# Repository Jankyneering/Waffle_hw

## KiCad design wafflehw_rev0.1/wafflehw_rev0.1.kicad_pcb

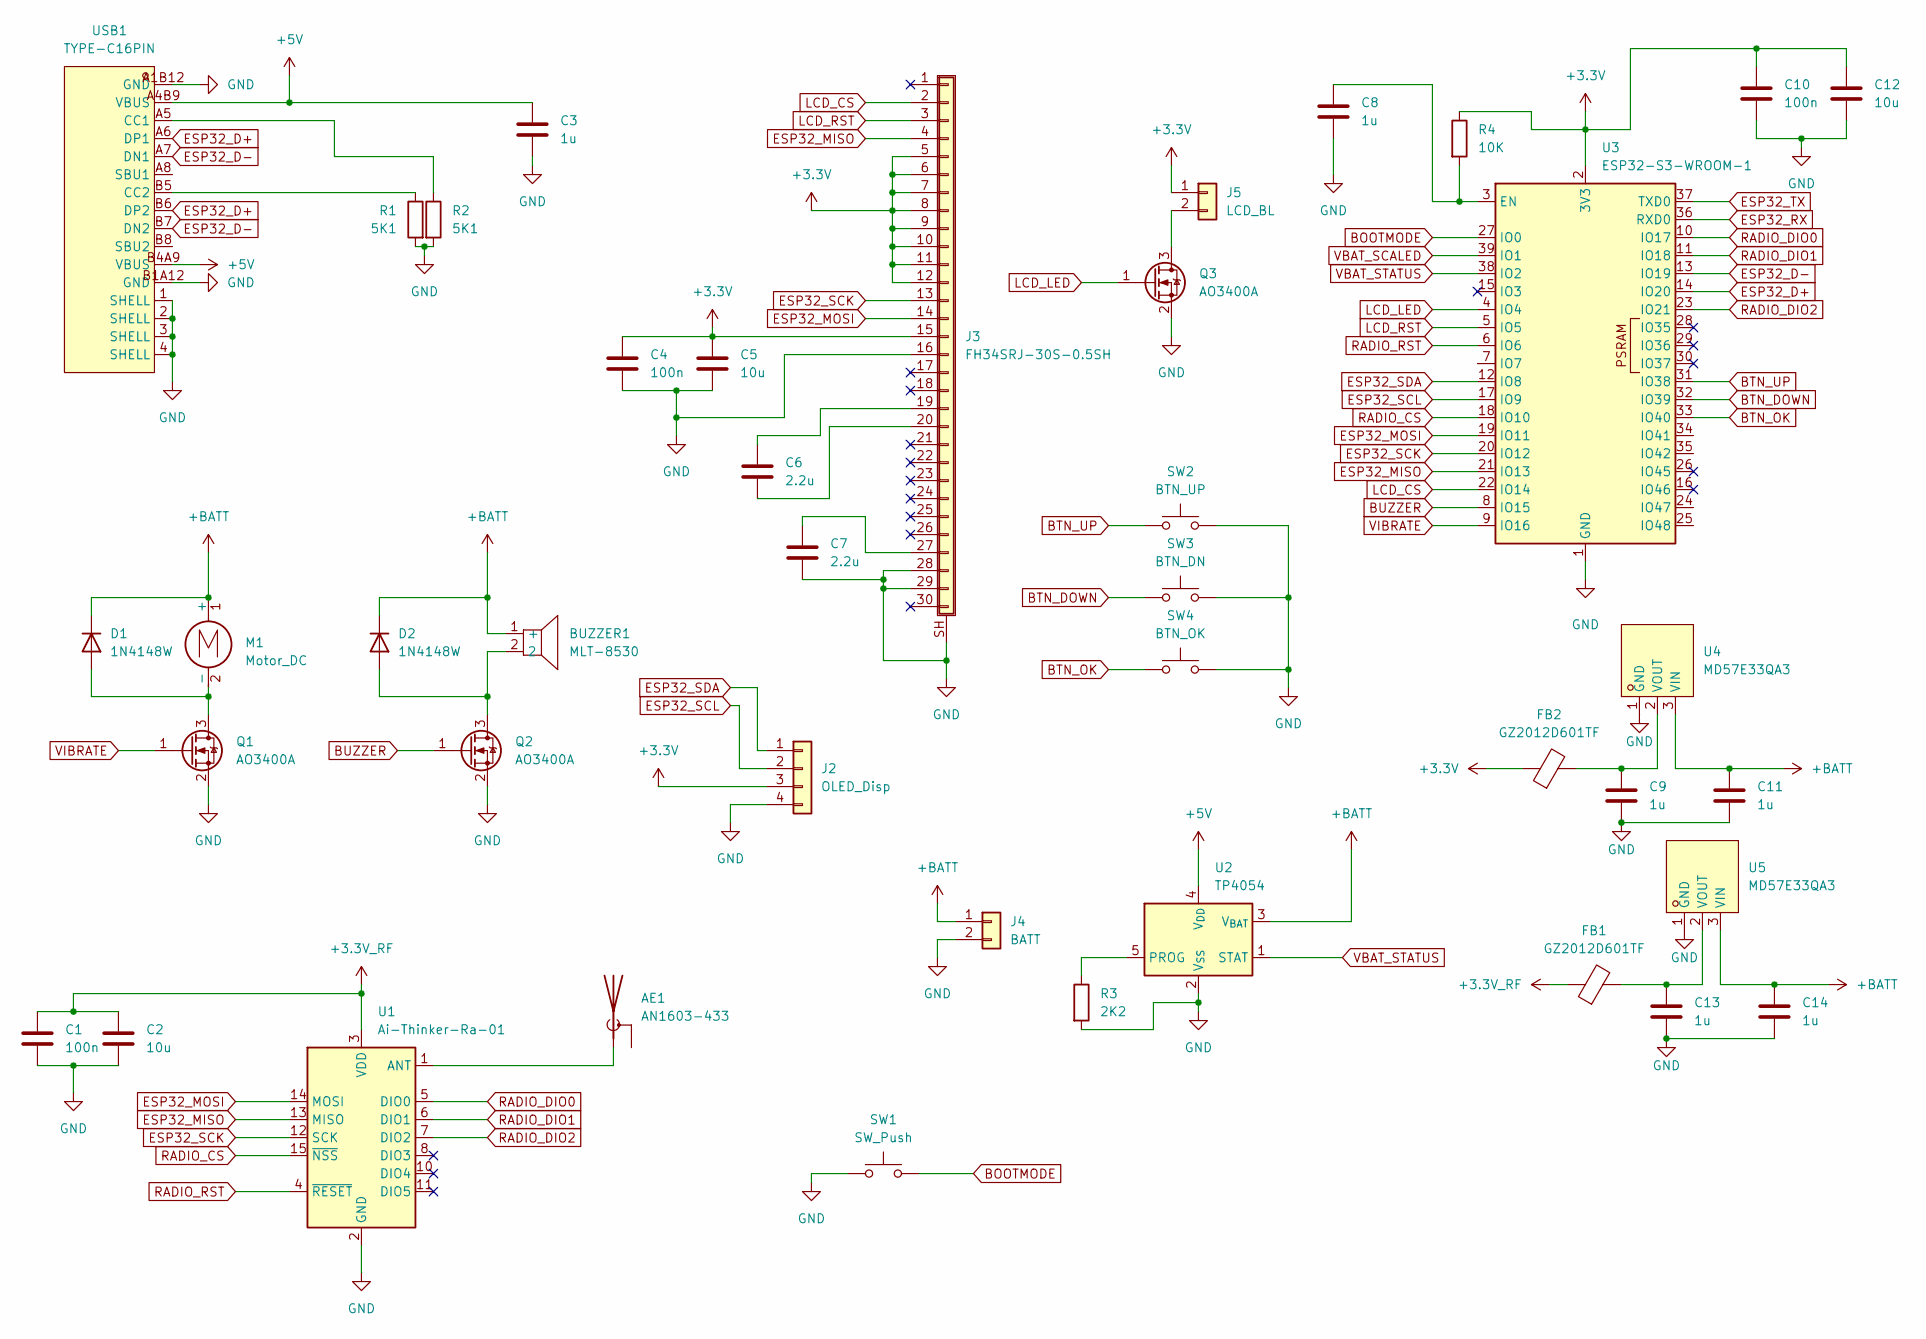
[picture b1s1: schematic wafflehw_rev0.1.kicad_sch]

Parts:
AE1: AN1603-433; Coilcraft_MA5532-AE_RFID
BUZZER1: MLT-8530; BUZ-SMD_4P-L8.5-W8.5-P8.50-BR; LCSC Part C94599
C1, C4, C10: 100n; C_0805_2012Metric
C2, C5, C12: 10u; C_0805_2012Metric
C3, C8, C9, C11, C13, C14: 1u; C_0805_2012Metric
C6, C7: 2.2u; C_0805_2012Metric
D1, D2: 1N4148W; D_SOD-123
FB1, FB2: GZ2012D601TF; L_0805_2012Metric
J2: OLED_Disp; PinHeader_1x04_P2.54mm_Vertical
J3: FH34SRJ-30S-0.5SH; ER-CON30HB-1
J4: BATT; ER-CON2.0-2P-SMD
J5: LCD_BL; ER-CON2.0-2P-SMD
M1: Motor_DC; SolderJumper-2_P1.3mm_Open_RoundedPad1.0x1.5mm
Q1, Q2, Q3: AO3400A; SOT-23
R1, R2: 5K1; C_0805_2012Metric
R3: 2K2; C_0805_2012Metric
R4: 10K; C_0805_2012Metric
SW1: SW_Push; SW_SPST_CK_RS282G05A3
SW2: BTN_UP; SW_SPST_CK_RS282G05A3
SW3: BTN_DN; SW_SPST_CK_RS282G05A3
SW4: BTN_OK; SW_SPST_CK_RS282G05A3
U1: Ai-Thinker-Ra-01; Ai-Thinker-Ra-01-LoRa
U2: TP4054; SOT-23-5
U3: ESP32-S3-WROOM-1
U4, U5: MD57E33QA3; SOT-23-3_L2.9-W1.6-P1.90-LS2.8-BR; LCSC Part C920553
USB1: TYPE-C16PIN; USB-C-SMD_TYPE-C16PIN; LCSC Part C393939

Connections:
+3.3V: C4.1, C5.1, C10.1, C12.1, FB2.1, J2.3, J3.5, J3.6, J3.7, J3.8, J3.9, J3.10, J3.11, J3.12, J3.15, J5.1, R4.1, U3.2 (3V3)
+3.3V_RF: C1.1, C2.1, FB1.1, U1.3 (VDD)
+5V: C3.1, U2.4 (V_{DD}), USB1.A4B9 (VBUS), USB1.B4A9 (VBUS)
+BATT: BUZZER1.1 (+), C11.1, C14.1, D1.1 (K), D2.1 (K), J4.1, M1.1 (+), U2.3 (V_{BAT}), U4.3 (VIN), U5.3 (VIN)
BOOTMODE: SW1.2, U3.27 (IO0)
BTN_DOWN: SW3.1, U3.32 (IO39)
BTN_OK: SW4.1, U3.33 (IO40)
BTN_UP: SW2.1, U3.31 (IO38)
BUZZER: Q2.1 (G), U3.8 (IO15)
ESP32_D+: U3.14 (IO20), USB1.A6 (DP1), USB1.B6 (DP2)
ESP32_D-: U3.13 (IO19), USB1.A7 (DN1), USB1.B7 (DN2)
ESP32_MISO: J3.4, U1.13 (MISO), U3.21 (IO13)
ESP32_MOSI: J3.14, U1.14 (MOSI), U3.19 (IO11)
ESP32_RX: U3.36 (RXD0)
ESP32_SCK: J3.13, U1.12 (SCK), U3.20 (IO12)
ESP32_SCL: J2.2, U3.17 (IO9)
ESP32_SDA: J2.1, U3.12 (IO8)
ESP32_TX: U3.37 (TXD0)
GND: C1.2, C2.2, C3.2, C4.2, C5.2, C7.2, C8.2, C9.2, C10.2, C11.2, C12.2, C13.2, C14.2, J2.4, J3.16, J3.28, J3.29, J3.SH (Shield), J4.2, Q1.2 (S), Q2.2 (S), Q3.2 (S), R1.2, R2.2, R3.2, SW1.1, SW2.2, SW3.2, SW4.2, U1.2 (GND), U1.9 (GND), U1.16 (GND), U2.2 (V_{SS}), U3.1 (GND), U3.40 (GND), U3.41 (GND), U4.1 (GND), U5.1 (GND), USB1.1 (SHELL), USB1.2 (SHELL), USB1.3 (SHELL), USB1.4 (SHELL), USB1.A1B12 (GND), USB1.B1A12 (GND)
LCD_CS: J3.2, U3.22 (IO14)
LCD_LED: Q3.1 (G), U3.4 (IO4)
LCD_RST: J3.3, U3.5 (IO5)
unnamed: AE1.1 (A), U1.1 (ANT)
unnamed: D1.2 (A), M1.2 (-), Q1.3 (D)
unnamed: BUZZER1.2, D2.2 (A), Q2.3 (D)
unnamed: C6.1, J3.19
unnamed: C6.2, J3.20
unnamed: C7.1, J3.27
unnamed: J5.2, Q3.3 (D)
unnamed: R3.1, U2.5 (PROG)
unnamed: C8.1, R4.2, U3.3 (EN)
unnamed: C9.1, FB2.2, U4.2 (VOUT)
unnamed: C13.1, FB1.2, U5.2 (VOUT)
unnamed: R2.1, USB1.A5 (CC1)
unnamed: R1.1, USB1.B5 (CC2)
RADIO_CS: U1.15 (~NSS), U3.18 (IO10)
RADIO_DIO0: U1.5 (DIO0), U3.10 (IO17)
RADIO_DIO1: U1.6 (DIO1), U3.11 (IO18)
RADIO_DIO2: U1.7 (DIO2), U3.23 (IO21)
RADIO_RST: U1.4 (~RESET), U3.6 (IO6)
VBAT_SCALED: U3.39 (IO1)
VBAT_STATUS: U2.1 (STAT), U3.38 (IO2)
VIBRATE: Q1.1 (G), U3.9 (IO16)

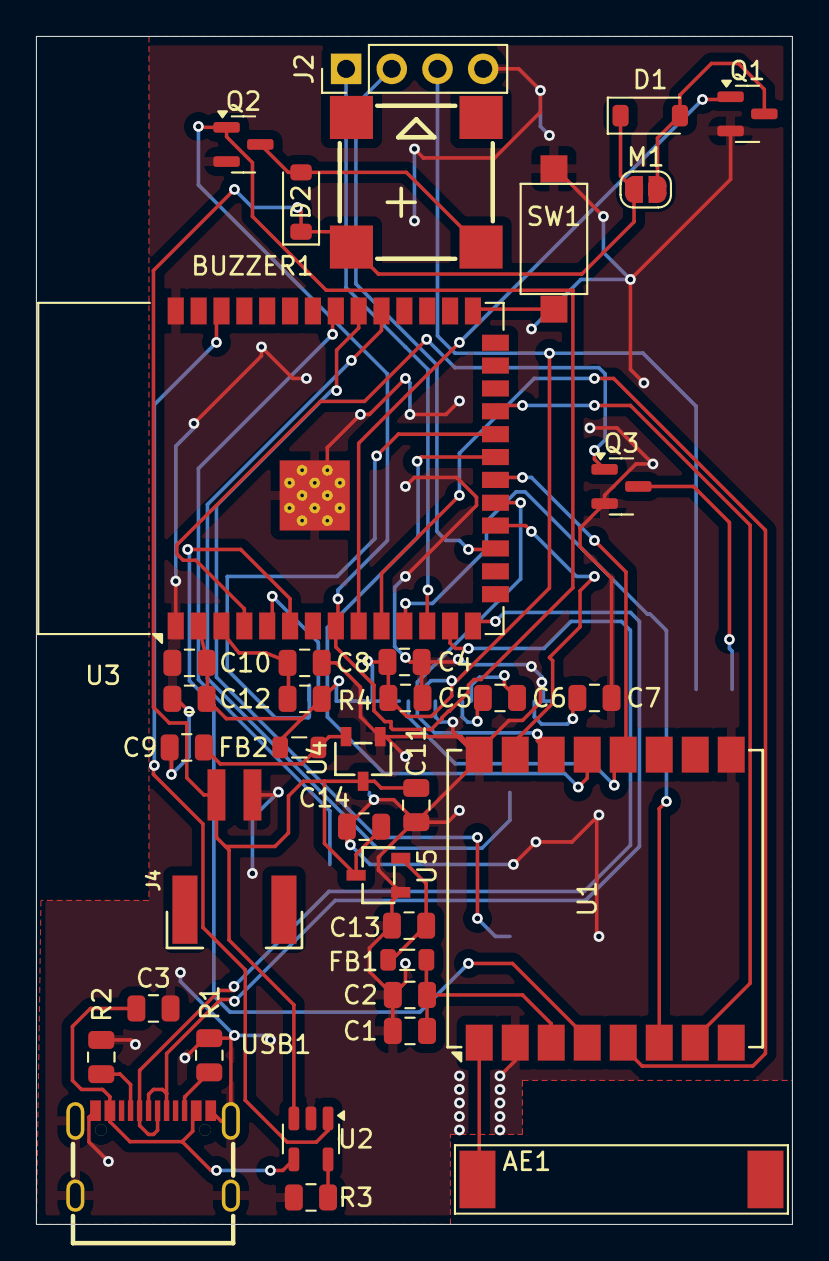
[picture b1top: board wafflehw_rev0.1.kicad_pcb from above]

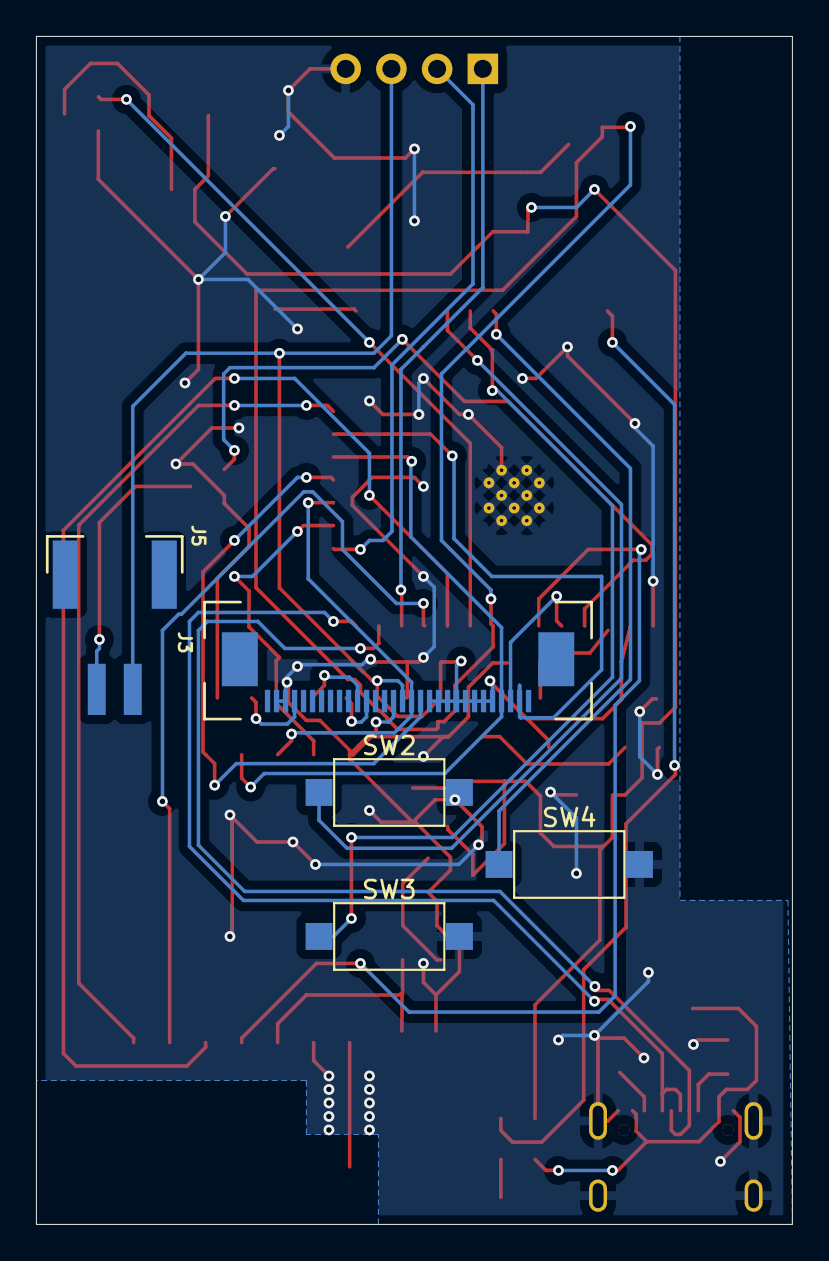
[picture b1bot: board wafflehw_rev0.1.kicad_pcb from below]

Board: 2 copper layers, 42.0 x 66.0 mm, 42 parts (5 on the bottom side), 40 nets.

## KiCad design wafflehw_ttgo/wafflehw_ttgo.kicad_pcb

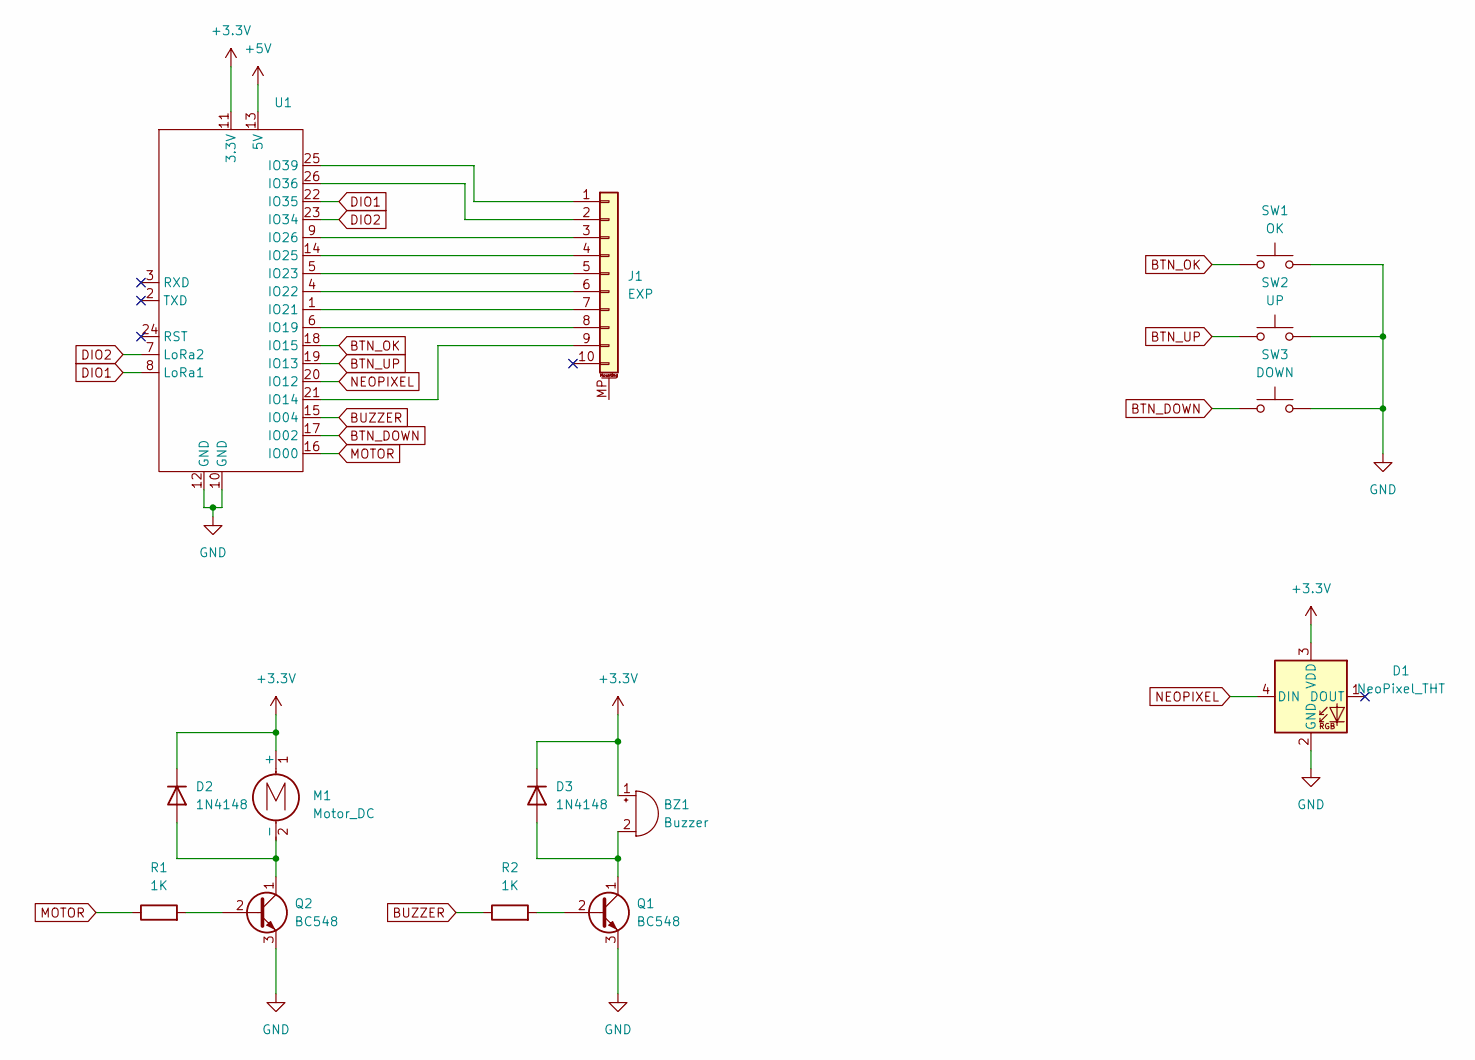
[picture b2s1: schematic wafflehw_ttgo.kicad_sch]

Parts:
BZ1: Buzzer; MagneticBuzzer_CUI_CST-931RP-A
D1: NeoPixel_THT; LED_D5.0mm-4_RGB
D2, D3: 1N4148; D_DO-35_SOD27_P7.62mm_Horizontal
J1: EXP; PinHeader_1x10_P2.54mm_Vertical
M1: Motor_DC; PinHeader_1x02_P2.54mm_Vertical
Q1, Q2: BC548; TO-92_Inline
R1, R2: 1K; R_Axial_DIN0207_L6.3mm_D2.5mm_P7.62mm_Horizontal
SW1: OK; SW_PUSH_6mm_H5mm
SW2: UP; SW_PUSH_6mm_H5mm
SW3: DOWN; SW_PUSH_6mm_H5mm
U1: TTGOLora32v2

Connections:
+3.3V: BZ1.1 (+), D1.3 (VDD), D2.1 (K), D3.1 (K), M1.1 (+), U1.11 (3.3V)
+5V: U1.13 (5V)
BTN_DOWN: SW3.1, U1.17 (IO02)
BTN_OK: SW1.1, U1.18 (IO15)
BTN_UP: SW2.1, U1.19 (IO13)
BUZZER: R2.1, U1.15 (IO04)
DIO1: U1.8 (LoRa1), U1.22 (IO35)
DIO2: U1.7 (LoRa2), U1.23 (IO34)
GND: D1.2 (GND), Q1.3 (E), Q2.3 (E), SW1.2, SW2.2, SW3.2, U1.10 (GND), U1.12 (GND)
MOTOR: R1.1, U1.16 (IO00)
NEOPIXEL: D1.4 (DIN), U1.20 (IO12)
unnamed: BZ1.2 (-), D3.2 (A), Q1.1 (C)
unnamed: D2.2 (A), M1.2 (-), Q2.1 (C)
unnamed: J1.1, U1.25 (IO39)
unnamed: J1.2, U1.26 (IO36)
unnamed: J1.3, U1.9 (IO26)
unnamed: J1.4, U1.14 (IO25)
unnamed: J1.5, U1.5 (IO23)
unnamed: J1.6, U1.4 (IO22)
unnamed: J1.7, U1.1 (IO21)
unnamed: J1.8, U1.6 (IO19)
unnamed: J1.9, U1.21 (IO14)
unnamed: Q1.2 (B), R2.2
unnamed: Q2.2 (B), R1.2

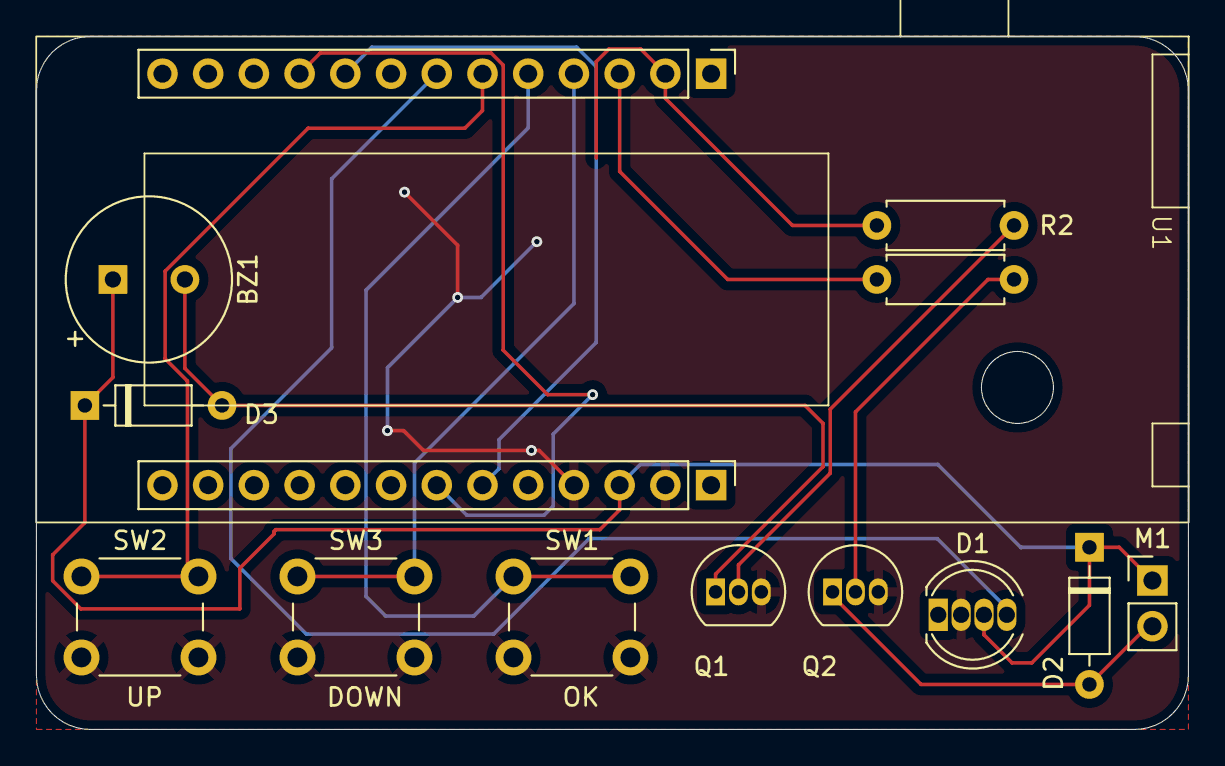
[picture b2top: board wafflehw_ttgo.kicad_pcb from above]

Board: 2 copper layers, 64.0 x 38.5 mm, 13 parts (0 on the bottom side), 14 nets.

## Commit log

2024-10-02 Added TTGO version
2024-10-02 Routed v 0.1
